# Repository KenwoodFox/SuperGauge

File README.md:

# SuperGauge

This repo contains all the firmware and hardware for the SuperGauge.

If you're looking for the latest docs/builds, see our [Releases Page](https://github.com/KenwoodFox/SuperGauge/releases).

# Getting Started

First, clone this repo (and optionally checkout a branch)

```shell
git clone https://github.com/KenwoodFox/SuperGauge.git
cd SuperGauge
```

# Init Submodules

Some libraries and resources are included as submodules, run the following
command to initialize them before opening the main sch

(If you get a missing library error, make sure to do this)

```shell
git submodule update --init --recursive
```

## Project Layout

If you want to use this project template for yourself, you can find it [here!](https://github.com/KenwoodFox/Project-Template)

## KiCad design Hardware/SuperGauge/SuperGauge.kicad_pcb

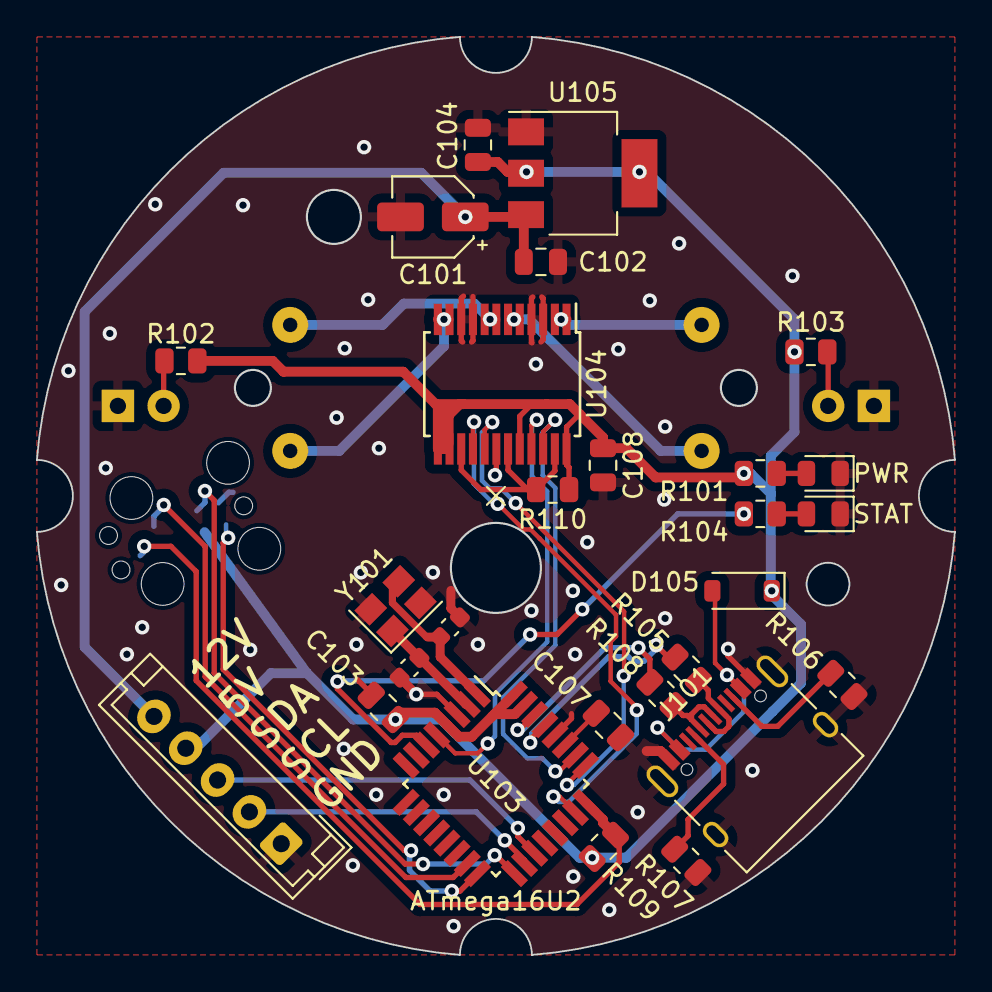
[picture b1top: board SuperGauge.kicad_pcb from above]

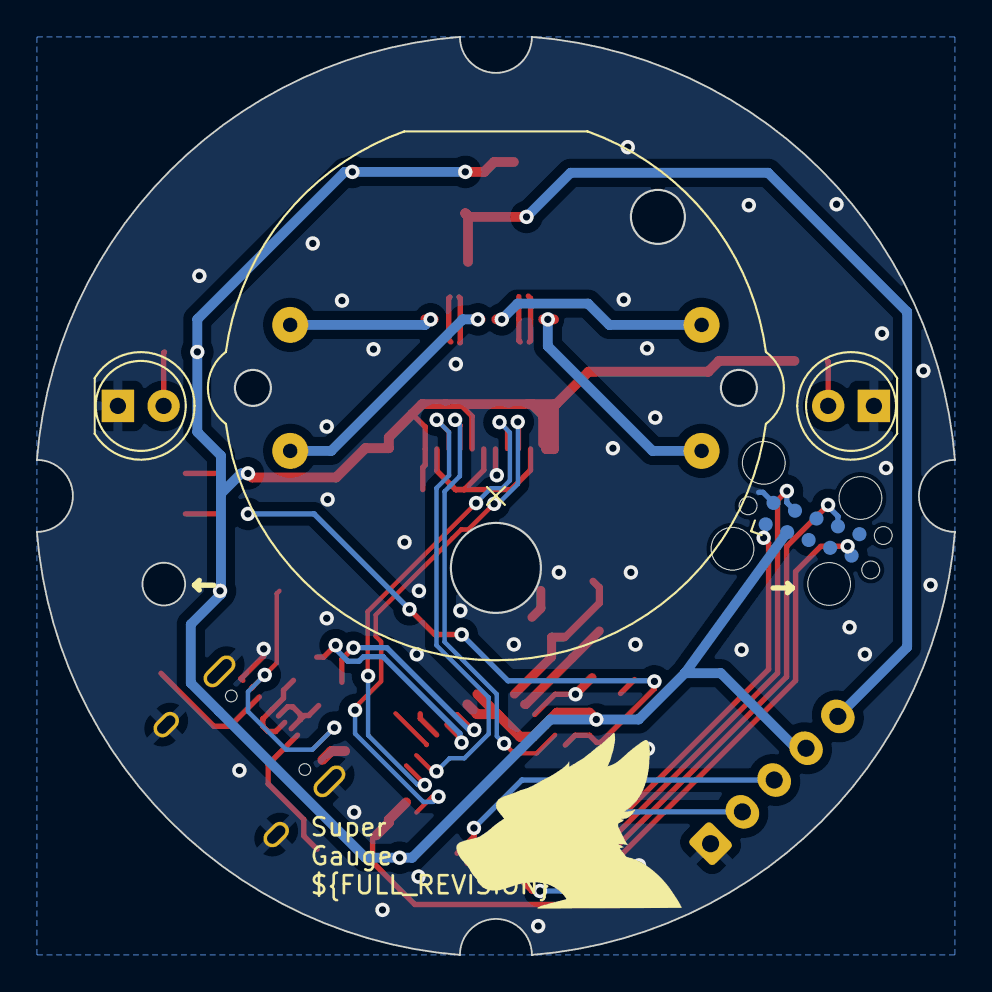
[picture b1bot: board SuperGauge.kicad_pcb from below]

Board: 2 copper layers, 51.0 x 51.0 mm, 31 parts (4 on the bottom side), 33 nets.

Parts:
C101: 10uf; CP_Elec_4x3
C102, C103: 100nF; C_0805_2012Metric
C104: 1uF; C_0805_2012Metric
C105, C106: 22pf; C_0603_1608Metric
C107, C108: 1u; C_0805_2012Metric
D101: PWR; LED_0805_2012Metric
D102, D103: BACKLIGHTING; LED_D5.0mm_Clear
D104: STAT; LED_0805_2012Metric
D105: MBR0520LT; D_SOD-123
J101: USBC; USB_C_Receptacle_XKB_U262-16XN-4BVC11_Full_Pads
J102: MainConn; JST_EH_B5B-EH-A_1x05_P2.50mm_Vertical
J103: Tag Connect; Tag-Connect_TC2050-IDC-FP_2x05_P1.27mm_Vertical
R101, R102, R103, R104: 1K; R_0805_2012Metric
R105, R108: 22R; R_0805_2012Metric
R106, R107: 5K1; R_0805_2012Metric
R109, R110: 10k; R_0805_2012Metric
U101: X27-168
U103: ATmega16U2; TQFP-32_7x7mm_P0.8mm
U104: TB6612FNG; SSOP-24_5.3x8.2mm_P0.65mm
U105: LM1117MP-5.0; SOT-223-3_TabPin2
Y101: Crystal_GND24; Crystal_SMD_3225-4Pin_3.2x2.5mm

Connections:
+5V: C103.1, C104.1, C108.1, D105.1 (K), J102.4, J103.2, R101.1, R102.1, R103.1, R109.2, R110.1, U103.4 (VCC), U103.31 (UVCC), U103.32 (AVCC), U104.13 (VM2), U104.14 (VM3), U104.20 (VCC), U104.24 (VM1), U105.2 (VO)
+12V: C101.1, C102.1, J102.5, U105.3 (VI)
/AIN1: U103.5 (PC2), U104.21 (AIN1)
/AIN2: U103.26 (PC4), U104.22 (AIN2)
/BIN1: U103.25 (PC5), U104.17 (BIN1)
/BIN2: U103.23 (PC6), U104.16 (BIN2)
/ICSP_MISO: J103.9, U103.17 (PB3)
/ICSP_MOSI: J103.1, U103.16 (PB2)
/ICSP_RST: J103.5, R109.1, U103.24 (PC1/~RESET)
/ICSP_SCK: J103.7, U103.15 (PB1)
/SCL: J102.2, U103.18 (PB4)
/SDA: J102.3, U103.19 (PB5)
/USB+: J101.A6 (D+), J101.B6 (D+), R105.1
/USB-: J101.A7 (D-), J101.B7 (D-), R108.1
/XTAL1: C106.1, U103.1 (XTAL1), Y101.3
/XTAL2: C105.1, U103.2 (PC0/XTAL2), Y101.1
GND: C101.2, C102.2, C103.2, C104.2, C105.2, C106.2, C107.2, C108.2, D101.1 (K), D102.1 (K), D103.1 (K), D104.1 (K), J101.A1 (GND), J101.A12 (GND), J101.B1 (GND), J101.B12 (GND), J101.S1 (SHIELD), J102.1, J103.10, R106.1, R107.1, U103.3 (GND), U103.28 (UGND), U104.3 (PGND1), U104.4 (PGND1), U104.9 (PGND2), U104.10 (PGND2), U104.18 (GND), U105.1 (GND), Y101.2, Y101.4
unnamed: D101.2 (A), R101.2
unnamed: D102.2 (A), R102.2
unnamed: D103.2 (A), R103.2
unnamed: D104.2 (A), R104.2
unnamed: D105.2 (A), J101.A4 (VBUS), J101.A9 (VBUS), J101.B4 (VBUS), J101.B9 (VBUS)
unnamed: J101.A5 (CC1), R107.2
unnamed: J101.B5 (CC2), R106.2
unnamed: U101.1, U104.1 (AO1), U104.2 (AO1)
unnamed: U101.2, U104.5 (AO2), U104.6 (AO2)
unnamed: U101.3, U104.11 (BO1), U104.12 (BO1)
unnamed: U101.4, U104.7 (BO2), U104.8 (BO2)
unnamed: R105.2, U103.29 (D+)
unnamed: R108.2, U103.30 (D-)
unnamed: R104.1, U103.6 (PD0)
unnamed: C107.1, U103.27 (UCAP)
unnamed: R110.2, U104.15 (PWMB), U104.19 (STBY), U104.23 (PWMA)

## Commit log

2023-09-07 Import from cookiecutter https://github.com/KenwoodFox/Project-Template
2023-09-07 Add upstream lib and new x27 motor
2023-09-07 Bump upstream again
2023-09-07 Bump gitignore
2023-09-07 Added in MCU
2023-09-08 More stuff
2023-09-08 Bump kibot
2023-09-11 More PCB stuff
2023-09-12 Stuff
2023-09-13 Bump design slightly
2023-09-13 Add motor driver
2023-09-14 Connect all
2023-09-14 Fix DRC
2023-09-15 RC time
2023-09-15 Hotfix
2023-09-15 Fix again
2023-09-15 Mark pre-release
2023-09-15 Add stencil marks
2023-09-15 Upload whatever
2023-09-18 Bump banner
2023-09-18 Test new from https://github.com/edunad/actions-image/issues/7\#issuecomment-1723659474
2023-09-18 Bump
2023-09-18 Bump perms
2023-09-18 fix perms
2023-09-18 Images and Fixed Dev Building (#1)
2023-09-18 Lockout dev pub
2023-09-19 This is on images now
2023-09-19 Add faceplate
2023-09-19 Bump with new comments in https://github.com/edunad/actions-image/issues/7
2023-09-19 Move Face to local path
2023-09-19 include improvements in upstream lib
2023-09-19 Fix Images (#2)
2023-09-28 Move mounting hole slightly
2023-09-28 Bump face
2023-09-28 Update workflows from template
2023-09-28 Include 3d models
2023-09-28 Remove step in wrong spot
2023-09-28 Create stencil
2023-09-29 Update and print face prototype
2023-09-29 use fcinfo
2023-09-29 Boilerplate legends
2023-09-29 DFU firmware mode?
2023-10-01 Bump face (again)
2023-11-30 Add cad, bump libs and more
2023-11-30 bump libs
